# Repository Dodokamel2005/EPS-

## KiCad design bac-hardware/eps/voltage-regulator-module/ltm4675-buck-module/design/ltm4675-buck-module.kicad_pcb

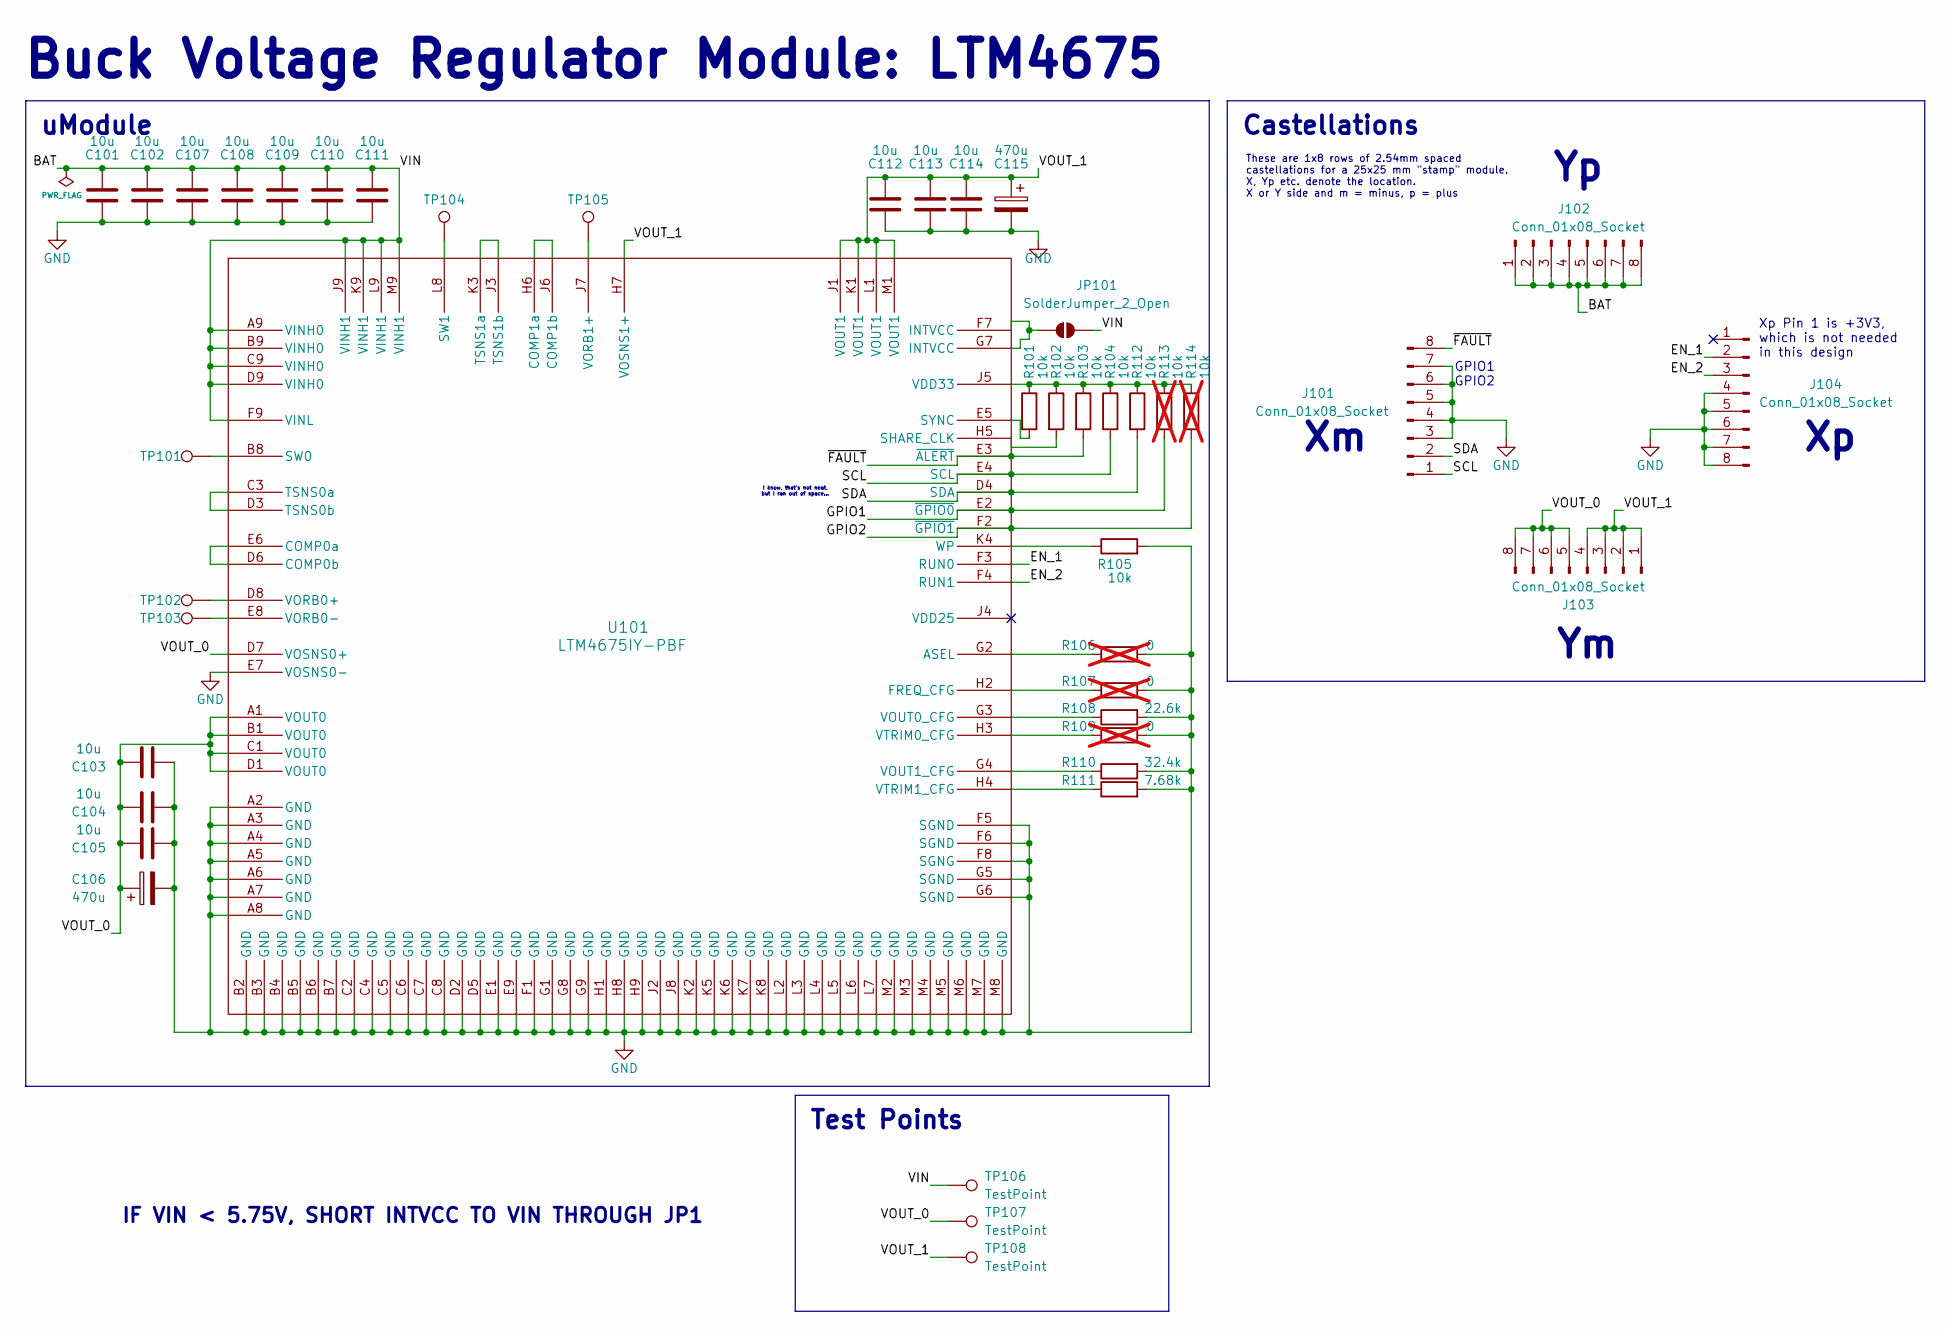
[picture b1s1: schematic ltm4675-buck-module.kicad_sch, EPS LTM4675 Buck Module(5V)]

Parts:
C101, C102, C103, C104, C105, C107, C108, C109, C110, C111, C112, C113, C114: 10u; C_0603_1608Metric; Tolerance 10%; Voltage Rating 25 V
C106, C115: 470u; CP_EIA-7343-15_Kemet-W; Tolerance 20%; Voltage Rating 6.3 V
J101, J102, J103, J104: Conn_01x08_Socket; bac-eps-v1-module-8P-pad-row
JP101: SolderJumper_2_Open; SolderJumper-2_P1.3mm_Open_TrianglePad1.0x1.5mm
R101, R102, R103, R104, R105, R112: 10k; R_0603_1608Metric
R106, R107, R109: 0; R_0603_1608Metric; Tolerance 1%; not fitted
R108: 22.6k; R_0603_1608Metric; Tolerance 1%
R110: 32.4k; R_0603_1608Metric; Tolerance 1%
R111: 7.68k; R_0603_1608Metric; Tolerance 1%
R113, R114: 10k; R_0201_0603Metric; not fitted
TP101, TP102, TP103, TP104, TP105, TP106, TP107, TP108: TestPoint; TestPoint_Pad_D1.0mm
U101: LTM4675IY-PBF; ADI-LTM4675IY

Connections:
/BAT: C101.1, C102.1, C107.1, C108.1, C109.1, C110.1, C111.1, J102.1, J102.2, J102.3, J102.4, J102.5, J102.6, J102.7, J102.8, JP101.2 (B), TP106.1, U101.A9 (VINH0), U101.B9 (VINH0), U101.C9 (VINH0), U101.D9 (VINH0), U101.F9 (VINL), U101.J9 (VINH1), U101.K9 (VINH1), U101.L9 (VINH1), U101.M9 (VINH1)
/EN_1: J104.2, U101.F3 (RUN0)
/EN_2: J104.3, U101.F4 (RUN1)
/GPIO1: R113.2, U101.E2 (~GPIO0)
/GPIO2: R114.2, U101.F2 (~GPIO1)
/SCL: J101.1, R104.2, U101.E4 (SCL)
/SDA: J101.2, R112.2, U101.D4 (SDA)
/VOUT_0: C103.1, C104.1, C105.1, C106.1, J103.5, J103.6, J103.7, J103.8, TP107.1, U101.A1 (VOUT0), U101.B1 (VOUT0), U101.C1 (VOUT0), U101.D1 (VOUT0), U101.D7 (VOSNS0+)
/VOUT_1: C112.1, C113.1, C114.1, C115.1, J103.1, J103.2, J103.3, J103.4, TP108.1, U101.H7 (VOSNS1+), U101.J1 (VOUT1), U101.K1 (VOUT1), U101.L1 (VOUT1), U101.M1 (VOUT1)
/~FAULT: J101.8, R103.2, U101.E3 (~ALERT)
GND: C101.2, C102.2, C103.2, C104.2, C105.2, C106.2, C107.2, C108.2, C109.2, C110.2, C111.2, C112.2, C113.2, C114.2, C115.2, J101.3, J101.4, J101.5, J101.6, J101.7, J104.4, J104.5, J104.6, J104.7, J104.8, R105.2, R106.2, R107.2, R108.2, R109.2, R110.2, R111.2, U101.A2 (GND), U101.A3 (GND), U101.A4 (GND), U101.A5 (GND), U101.A6 (GND), U101.A7 (GND), U101.A8 (GND), U101.B2 (GND), U101.B3 (GND), U101.B4 (GND), U101.B5 (GND), U101.B6 (GND), U101.B7 (GND), U101.C2 (GND), U101.C4 (GND), U101.C5 (GND), U101.C6 (GND), U101.C7 (GND), U101.C8 (GND), U101.D2 (GND), U101.D5 (GND), U101.E1 (GND), U101.E7 (VOSNS0-), U101.E9 (GND), U101.F1 (GND), U101.F5 (SGND), U101.F6 (SGND), U101.F8 (SGNG), U101.G1 (GND), U101.G5 (SGND), U101.G6 (SGND), U101.G8 (GND), U101.G9 (GND), U101.H1 (GND), U101.H8 (GND), U101.H9 (GND), U101.J2 (GND), U101.J8 (GND), U101.K2 (GND), U101.K5 (GND), U101.K6 (GND), U101.K7 (GND), U101.K8 (GND), U101.L2 (GND), U101.L3 (GND), U101.L4 (GND), U101.L5 (GND), U101.L6 (GND), U101.L7 (GND), U101.M2 (GND), U101.M3 (GND), U101.M4 (GND), U101.M5 (GND), U101.M6 (GND), U101.M7 (GND), U101.M8 (GND)
unnamed: JP101.1 (A), U101.F7 (INTVCC), U101.G7 (INTVCC)
unnamed: R106.1, U101.G2 (ASEL)
unnamed: U101.D6 (COMP0b), U101.E6 (COMP0a)
unnamed: U101.H6 (COMP1a), U101.J6 (COMP1b)
unnamed: R107.1, U101.H2 (FREQ_CFG)
unnamed: R102.2, U101.H5 (SHARE_CLK)
unnamed: TP101.1, U101.B8 (SW0)
unnamed: TP104.1, U101.L8 (SW1)
unnamed: R101.2, U101.E5 (SYNC)
unnamed: U101.C3 (TSNS0a), U101.D3 (TSNS0b)
unnamed: U101.J3 (TSNS1b), U101.K3 (TSNS1a)
unnamed: R101.1, R102.1, R103.1, R104.1, R112.1, R113.1, R114.1, U101.J5 (VDD33)
unnamed: TP102.1, U101.D8 (VORB0+)
unnamed: TP103.1, U101.E8 (VORB0-)
unnamed: TP105.1, U101.J7 (VORB1+)
unnamed: R108.1, U101.G3 (VOUT0_CFG)
unnamed: R110.1, U101.G4 (VOUT1_CFG)
unnamed: R109.1, U101.H3 (VTRIM0_CFG)
unnamed: R111.1, U101.H4 (VTRIM1_CFG)
unnamed: R105.1, U101.K4 (WP)

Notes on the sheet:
These are 1x8 rows of 2.54mm spaced castellations for a 25x25 mm "stamp" module. X, Yp etc. denote the location. X or Y side and m = minus, p = plus
I know, that's not neat, but I ran out of space...
IF VIN < 5.75V, SHORT INTVCC TO VIN THROUGH JP1
Xp Pin 1 is +3V3, which is not needed in this design
GPIO1 GPIO2
Buck Voltage Regulator Module: LTM4675
Test Points
uModule
Castellations

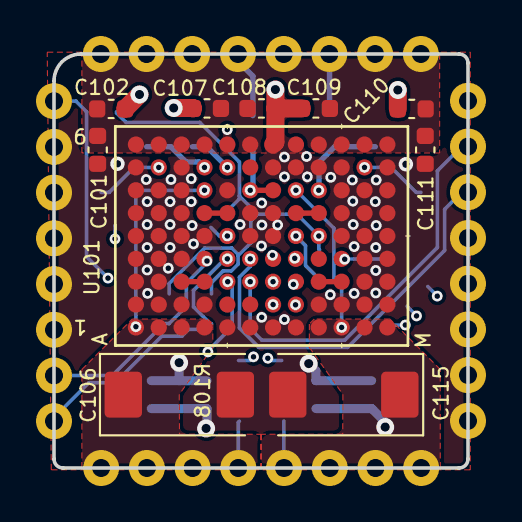
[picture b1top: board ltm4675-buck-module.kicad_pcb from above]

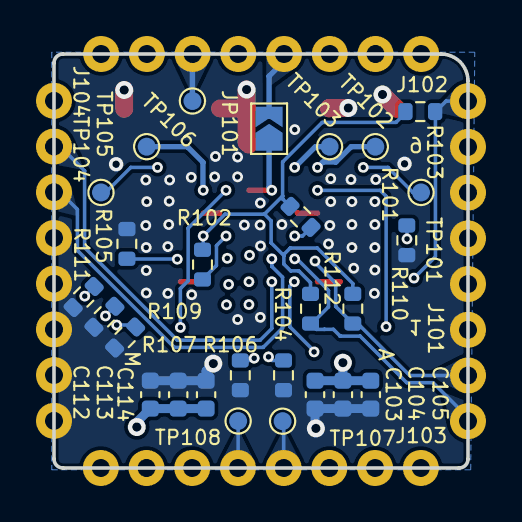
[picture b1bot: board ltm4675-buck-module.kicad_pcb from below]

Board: 4 copper layers, 23.0 x 23.0 mm, 41 parts (27 on the bottom side), 29 nets.

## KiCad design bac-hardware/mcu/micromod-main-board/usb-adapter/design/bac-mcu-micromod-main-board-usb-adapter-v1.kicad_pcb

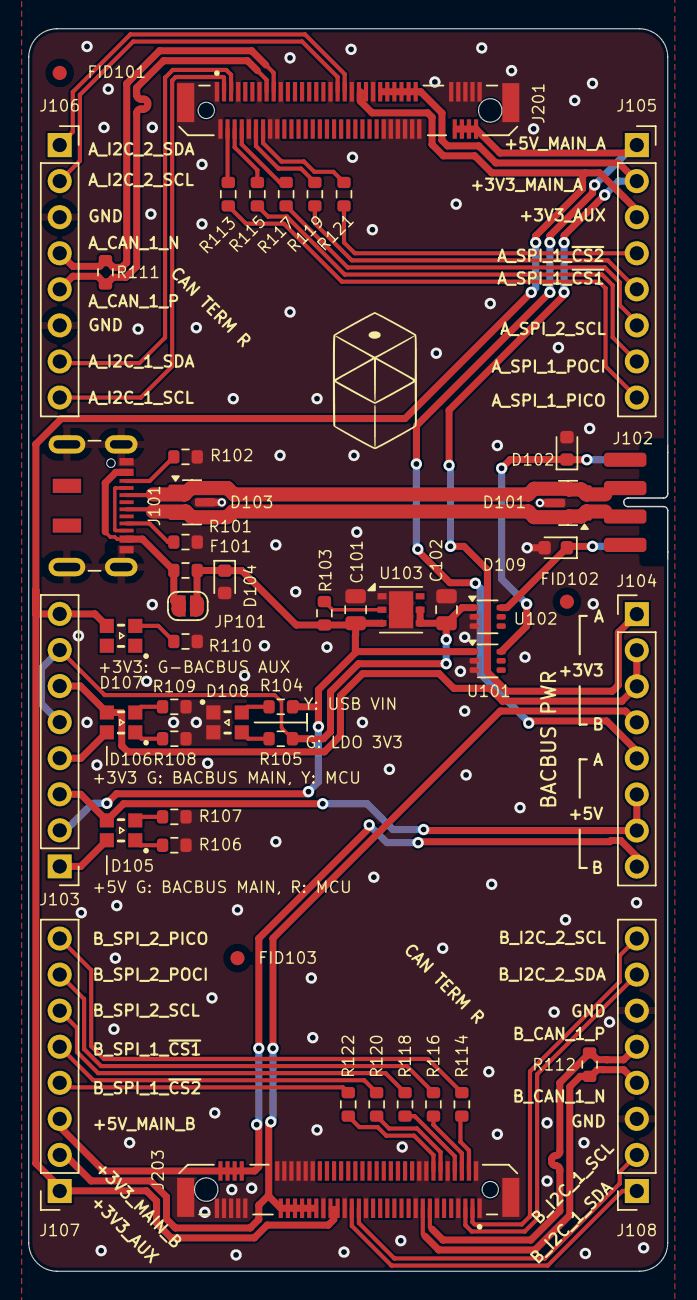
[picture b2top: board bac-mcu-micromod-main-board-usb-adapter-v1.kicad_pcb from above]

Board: 2 copper layers, 45.0 x 87.5 mm, 51 parts (0 on the bottom side), 59 nets.

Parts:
C101, C102: 10u; C_0805_2012Metric
D101, D103: TI ESD752; SOT-23
D102, D104, D109: ESD751; D_0603_1608Metric
D105, D106, D107, D108: WE 150080SG54050; WE-150080XX54050
F101: 0603L200SL-VYR; R_0603_1608Metric
FID101, FID102, FID103: Fiducial; Fiducial_1mm_Mask2mm
J101: USB_C_Receptacle_USB2.0_14P; JAE-DX07S016JA1R1500
J102: Conn_02x04_Top_Bottom; bac-KYO-00-9159-BTB
J103, J104: Conn_01x08_Pin; PinHeader_1x08_P2.54mm_Vertical
J105, J106, J107, J108: Conn_01x08_Socket; PinSocket_1x08_P2.54mm_Vertical
J201: AMP MDT350M01001VT; AMP-MDT350M01001VT
J203: BMP MDT350M01001VT; AMP-MDT350M01001VT
JP101: SolderJumper_2_Open; SolderJumper-2_P1.3mm_Open_RoundedPad1.0x1.5mm
R101, R102, R103: 5k1; R_0603_1608Metric
R104, R105, R106, R107, R108, R109, R110, R111, R112: 120; R_0603_1608Metric
R113, R114, R117, R118, R119, R120, R121, R122: R0; R_0603_1608Metric
R115, R116: 10; R_0603_1608Metric
U101, U102: LM66100DCK; SOT-363_SC-70-6
U103: LDO40LPU33RY; DFN-6-1EP_3x3mm_P0.95mm_EP1.7x2.6mm

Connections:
+3V3: C102.1, J103.5, J103.7, R105.1, U102.1 (VIN), U103.4 (VOUT), U103.5 (SENSE)
/3V3_OUT: D109.1 (K), J102.8, U102.6 (VOUT)
/5V_OUT: D102.1 (K), J102.5, U101.6 (VOUT)
/D+: D101.1 (K), D103.2 (K), J101.B6 (D+), J102.3
/D-: D101.2 (K), D103.1 (K), J101.B7 (D-), J102.2
/MAMOD_+3V3_AUX: D107.3, J103.8, J105.3, J107.1, J201.41, J201.43, J203.41, J203.43
/MAMOD_+3V3_MAIN: D106.3, J103.6, J104.2, J104.3
/MAMOD_+3V3_MAIN_A: J104.1, J105.2, J201.47, J201.49, J201.51, J201.53, J201.55, J201.57
/MAMOD_+3V3_MAIN_B: J104.4, J107.2, J203.47, J203.49, J203.51, J203.53, J203.55, J203.57
/MAMOD_+5V_MAIN: D105.3, J103.3, J104.6, J104.7
/MAMOD_+5V_MAIN_A: J104.5, J105.1, J201.68, J201.70, J201.72, J201.74
/MAMOD_+5V_MAIN_B: J104.8, J107.3, J203.68, J203.70, J203.72, J203.74
/MAMOD_A_CAN_1_N: J106.4, J201.17, R111.2
/MAMOD_A_CAN_1_P: J106.5, J201.15, R111.1
/MAMOD_A_I2C_1_SCL: J106.8, J201.3
/MAMOD_A_I2C_1_SDA: J106.7, J201.5
/MAMOD_A_I2C_2_SCL: J106.2, J201.35
/MAMOD_A_I2C_2_SDA: J106.1, J201.37
/MAMOD_A_SPI_1_~CS_1: J105.5, R119.1
/MAMOD_A_SPI_1_~CS_2: J105.4, R121.1
/MAMOD_B_CAN_1_N: J108.4, J203.17, R112.2
/MAMOD_B_CAN_1_P: J108.5, J203.15, R112.1
/MAMOD_B_I2C_1_SCL: J108.8, J203.3
/MAMOD_B_I2C_1_SDA: J108.7, J203.5
/MAMOD_B_I2C_2_SCL: J108.2, J203.35
/MAMOD_B_I2C_2_SDA: J108.1, J203.37
/MAMOD_B_SPI_1_~CS_1: J107.5, R120.1
/MAMOD_B_SPI_1_~CS_2: J107.4, R122.1
/MCU_+3V3: D106.4, J103.4
/MCU_+5V: D105.4, J103.1
/SPI_1_PICO: J105.8, R113.1
/SPI_1_POCI: J105.7, R115.1
/SPI_1_SCL: J105.6, R117.1
/SPI_2_PICO: J107.8, R114.1
/SPI_2_POCI: J107.7, R116.1
/SPI_2_SCL: J107.6, R118.1
/bacBus Connectors/3A: J201.4, R113.2
/bacBus Connectors/3B: J203.4, R114.2
/bacBus Connectors/5A: J201.6, R115.2
/bacBus Connectors/5B: J203.6, R116.2
/bacBus Connectors/7A: J201.8, R117.2
/bacBus Connectors/7B: J203.8, R118.2
/bacBus Connectors/11A: J201.12, R119.2
/bacBus Connectors/11B: J203.12, R120.2
/bacBus Connectors/13A: J201.14, R121.2
/bacBus Connectors/13B: J203.14, R122.2
GND: C101.2, C102.2, D101.3 (A), D102.2 (A), D103.3 (A), D104.2 (A), D108.1, D108.2, D109.2 (A), J101.A1 (GND), J101.A12 (GND), J101.B1 (GND), J101.B12 (GND), J101.S1 (SHIELD), J102.6, J102.7, J106.3, J106.6, J108.3, J108.6, J201.1, J201.2, J201.7, J201.10, J201.13, J201.16, J201.18, J201.19, J201.33, J201.39, J201.45, J201.48, J201.50, J201.52, J201.54, J201.56, J201.58, J201.67, J201.69, J201.71, J201.73, J201.75, J201.S1 (SHIELD), J201.S2 (SHIELD__1), J203.1, J203.2, J203.7, J203.10, J203.13, J203.16, J203.18, J203.19, J203.33, J203.39, J203.45, J203.48, J203.50, J203.52, J203.54, J203.56, J203.58, J203.67, J203.69, J203.71, J203.73, J203.75, J203.S1 (SHIELD), J203.S2 (SHIELD__1), R101.2, R102.2, R106.2, R107.2, R108.2, R109.2, R110.2, U101.2 (GND), U101.3 (~CE), U102.2 (GND), U102.3 (~CE), U103.1 (GND), U103.7 (EPAD)
unnamed: D105.1, R106.1
unnamed: D105.2, R107.1
unnamed: D106.1, R108.1
unnamed: D106.2, R109.1
unnamed: D107.2, R110.1
unnamed: D108.3, R105.2
unnamed: D108.4, R104.2
unnamed: J101.A5 (CC1), R102.1
unnamed: J101.B5 (CC2), R101.1
unnamed: R103.1, U103.2 (EN)
USB_VIN: C101.1, D104.1 (K), F101.2, J103.2, JP101.2 (B), R103.2, R104.1, U101.1 (VIN), U103.3 (VIN)
VBUS: F101.1, J101.A4 (VBUS), J101.A9 (VBUS), J101.B4 (VBUS), J101.B9 (VBUS), JP101.1 (A)

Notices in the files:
bac-hardware/eps/voltage-regulator-module/ltm4675-buck-module/design/ltm4675-buck-module.kicad_pcb:
CC BY-SA 4.0
